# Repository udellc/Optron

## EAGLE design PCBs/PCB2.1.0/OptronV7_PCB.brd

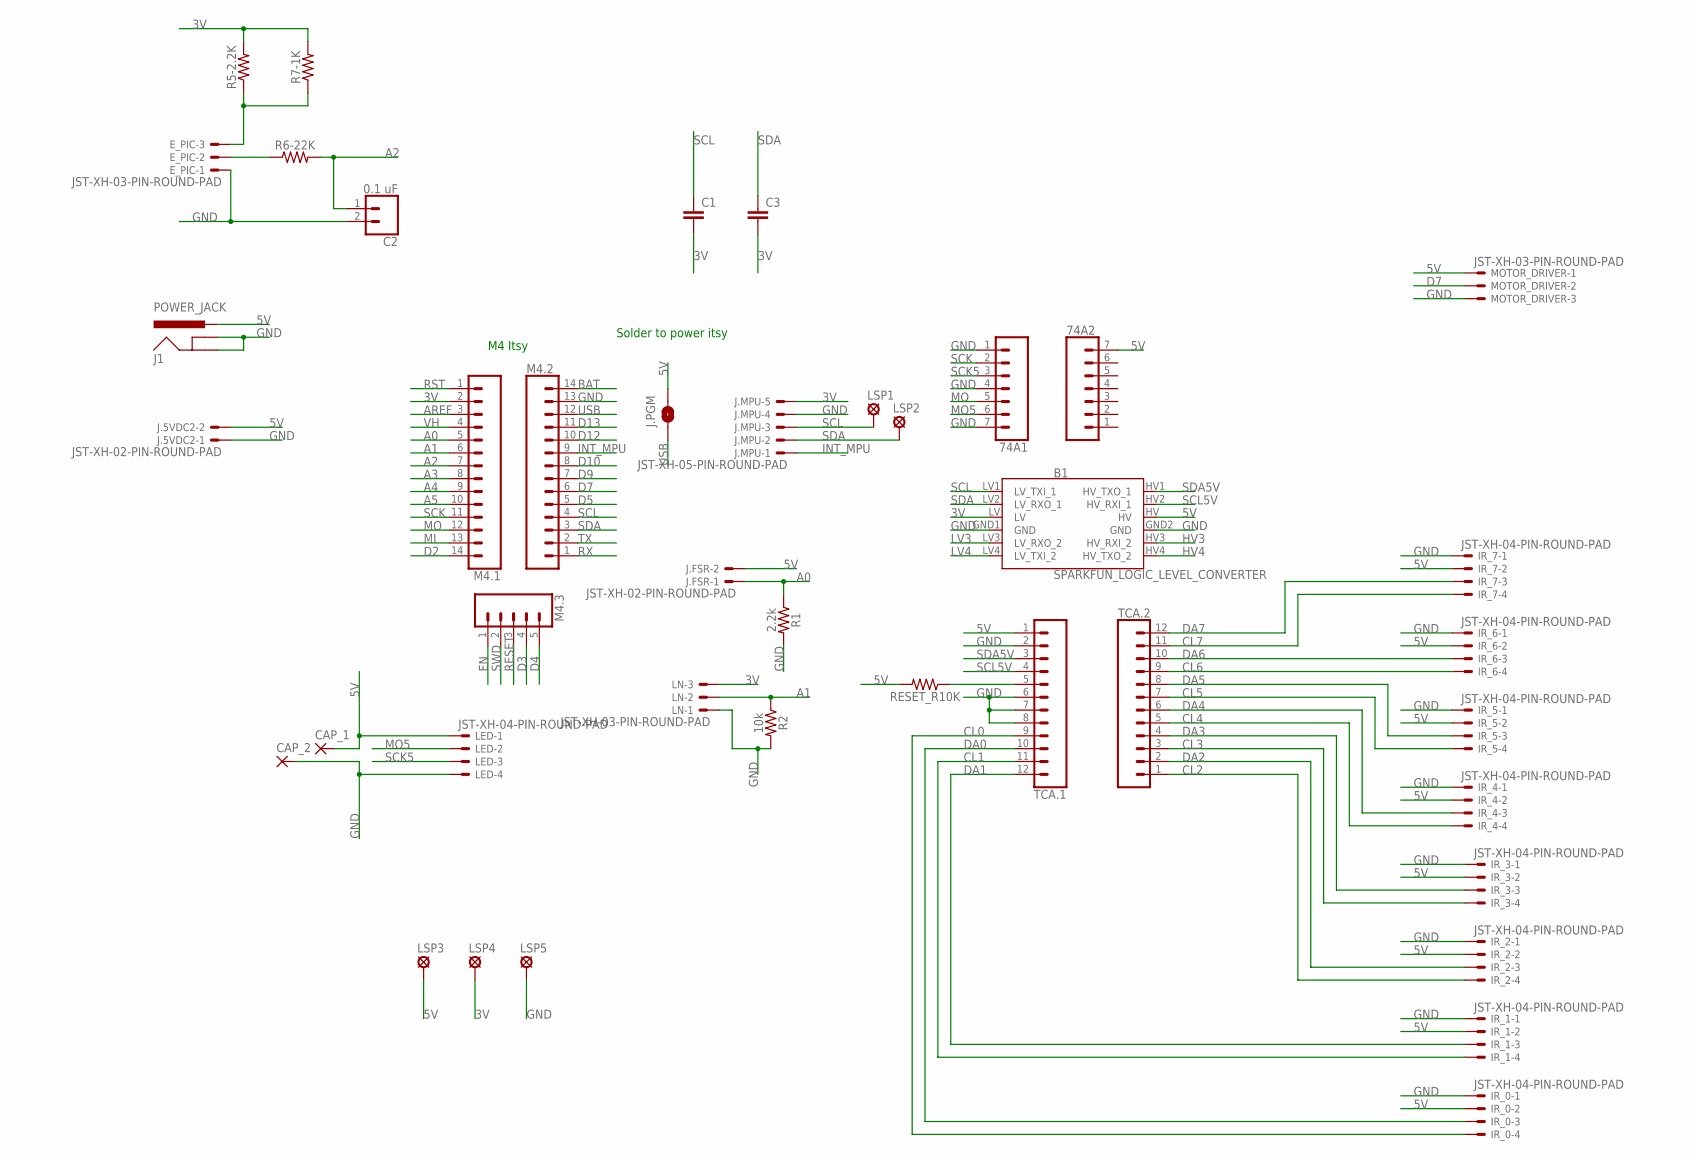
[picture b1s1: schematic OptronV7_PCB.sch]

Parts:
74A1, 74A2: CONN_07; 1X07
B1: SPARKFUN_LOGIC_LEVEL_CONVERTER
C1, C3: C5/2.5; C5B2.5
C2: 0.1 uF; 1X02
CAP_1, CAP_2: 1,6/0,8
E_PIC: JST-XH-03-PIN-ROUND-PAD; JST-XH-03-PACKAGE-ROUND-PAD
IR_0, IR_1, IR_2, IR_3, IR_4, IR_5, IR_6, IR_7: JST-XH-04-PIN-ROUND-PAD; JST-XH-04-PACKAGE-ROUND-PAD
J1: POWER_JACK; POWER_JACK_PTH
J.5VDC2, J.FSR: JST-XH-02-PIN-ROUND-PAD; JST-XH-02-PACKAGE-ROUND-PAD
J.MPU: JST-XH-05-PIN-ROUND-PAD; JST-XH-05-PACKAGE-ROUND-PAD
J.PGM: JUMPER-SMT_2_NO_NO-SILK; SMT-JUMPER_2_NO_NO-SILK
LED: JST-XH-04-PIN-ROUND-PAD; JST-XH-04-PACKAGE-ROUND-PAD
LN: JST-XH-03-PIN-ROUND-PAD; JST-XH-03-PACKAGE-ROUND-PAD
LSP1, LSP2, LSP3, LSP4, LSP5: MCS08
M4.1, M4.2: CONN_14; 1X14
M4.3: CONN_05; 1X05
MOTOR_DRIVER: JST-XH-03-PIN-ROUND-PAD; JST-XH-03-PACKAGE-ROUND-PAD
R1: 2.2k; AXIAL-0.3
R2: 10k; AXIAL-0.3
R5-2.2K, R6-22K, R7-1K: AXIAL-0.3
RESET_R10K: AXIAL-0.3
TCA.1, TCA.2: CONN_12; 1X12

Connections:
3V: B1.LV, C1.2, C3.2, J.MPU.5, LN.3, LSP4.MP, M4.1.2, R5-2.2K.P$2 (2), R7-1K.P$2 (2)
5V: 74A2.7, B1.HV, CAP_1.1, IR_0.2, IR_1.2, IR_2.2, IR_3.2, IR_4.2, IR_5.2, IR_6.2, IR_7.2, J1.PWR, J.5VDC2.2, J.FSR.2, J.PGM.2, LED.1, LSP3.MP, MOTOR_DRIVER.1, RESET_R10K.P$2 (2), TCA.1.1
A0: J.FSR.1, M4.1.5, R1.P$1 (1)
A1: LN.2, M4.1.6, R2.P$1 (1)
A2: C2.1, M4.1.7, R6-22K.P$2 (2)
A3: M4.1.8
A4: M4.1.9
A5: M4.1.10
AREF: M4.1.3
BAT: M4.2.14
CL0: IR_0.4, TCA.1.9
CL1: IR_1.4, TCA.1.11
CL2: IR_2.4, TCA.2.1
CL3: IR_3.4, TCA.2.3
CL4: IR_4.4, TCA.2.5
CL5: IR_5.4, TCA.2.7
CL6: IR_6.4, TCA.2.9
CL7: IR_7.4, TCA.2.11
D2: M4.1.14
D3: M4.3.4
D4: M4.3.5
D5: M4.2.5
D7: M4.2.6, MOTOR_DRIVER.2
D9: M4.2.7
D10: M4.2.8
D12: M4.2.10
D13: M4.2.11
DA0: IR_0.3, TCA.1.10
DA1: IR_1.3, TCA.1.12
DA2: IR_2.3, TCA.2.2
DA3: IR_3.3, TCA.2.4
DA4: IR_4.3, TCA.2.6
DA5: IR_5.3, TCA.2.8
DA6: IR_6.3, TCA.2.10
DA7: IR_7.3, TCA.2.12
EN: M4.3.1
GND: 74A1.1, 74A1.4, 74A1.7, B1.GND1 (GND), B1.GND2 (GND), C2.2, CAP_2.1, E_PIC.1, IR_0.1, IR_1.1, IR_2.1, IR_3.1, IR_4.1, IR_5.1, IR_6.1, IR_7.1, J1.GND, J1.GNDBREAK, J.5VDC2.1, J.MPU.4, LED.4, LN.1, LSP5.MP, M4.2.13, MOTOR_DRIVER.3, R1.P$2 (2), R2.P$2 (2), TCA.1.2, TCA.1.6, TCA.1.7, TCA.1.8
HV3: B1.HV3 (HV_RXI_2)
HV4: B1.HV4 (HV_TXO_2)
INT_MPU: J.MPU.1, M4.2.9
LV3: B1.LV3 (LV_RXO_2)
LV4: B1.LV4 (LV_TXI_2)
MI: M4.1.13
MO: 74A1.5, M4.1.12
MO5: 74A1.6, LED.2
unnamed: RESET_R10K.P$1 (1), TCA.1.5
unnamed: E_PIC.3, R5-2.2K.P$1 (1), R7-1K.P$1 (1)
unnamed: E_PIC.2, R6-22K.P$1 (1)
RESET: M4.3.3
RST: M4.1.1
RX: M4.2.1
SCK: 74A1.2, M4.1.11
SCK5: 74A1.3, LED.3
SCL: B1.LV1 (LV_TXI_1), C1.1, J.MPU.3, LSP1.MP, M4.2.4
SCL5V: B1.HV2 (HV_RXI_1), TCA.1.4
SDA: B1.LV2 (LV_RXO_1), C3.1, J.MPU.2, LSP2.MP, M4.2.3
SDA5V: B1.HV1 (HV_TXO_1), TCA.1.3
SWD: M4.3.2
TX: M4.2.2
USB: J.PGM.1, M4.2.12
VH: M4.1.4

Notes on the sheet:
M4 Itsy
Solder to power itsy

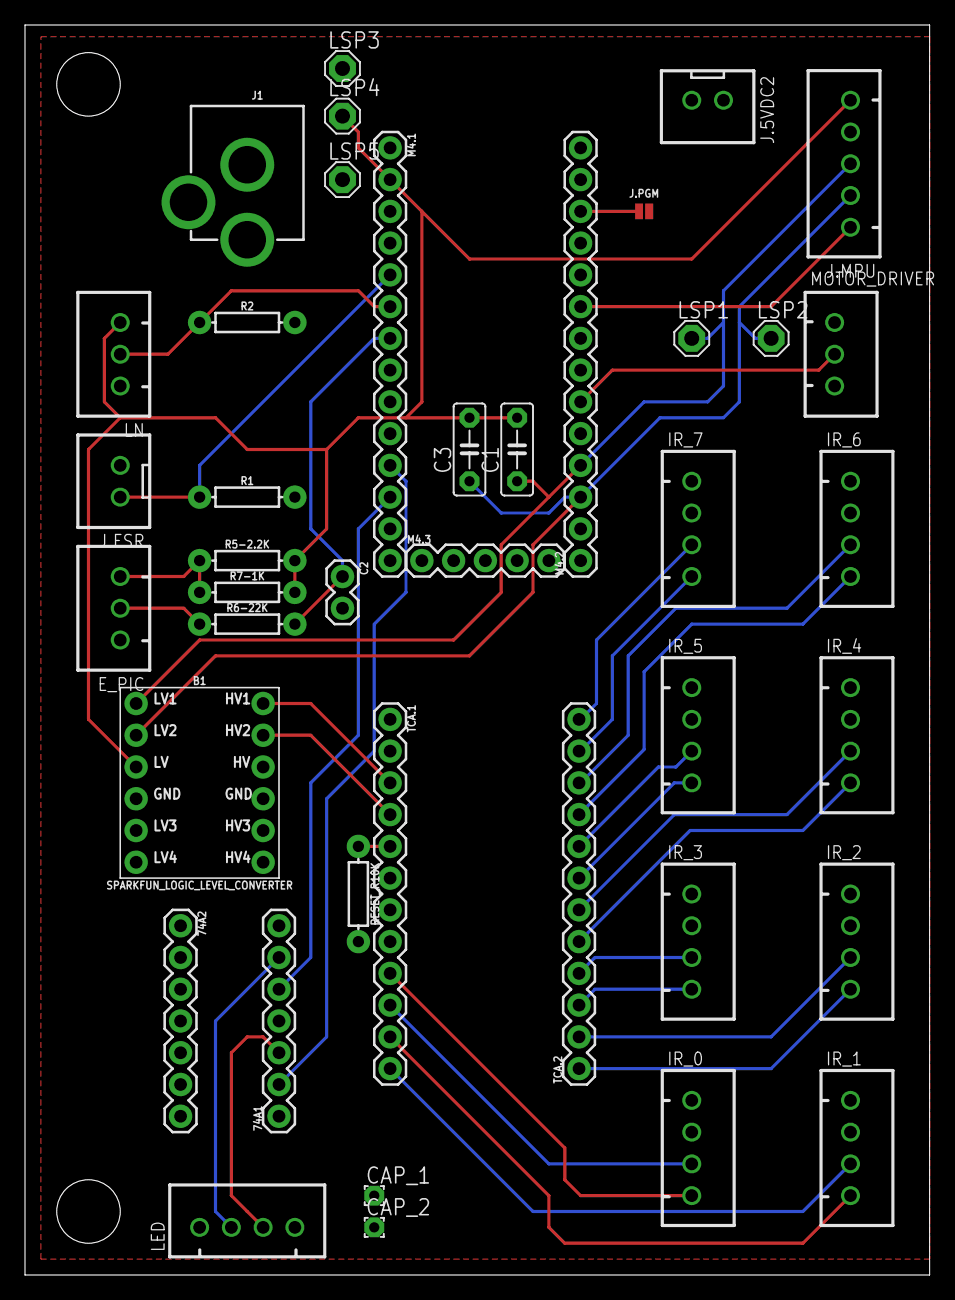
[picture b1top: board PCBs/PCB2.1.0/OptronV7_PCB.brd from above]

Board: 2 copper layers, 72.4 x 100.0 mm, 41 parts (0 on the bottom side), 36 nets.

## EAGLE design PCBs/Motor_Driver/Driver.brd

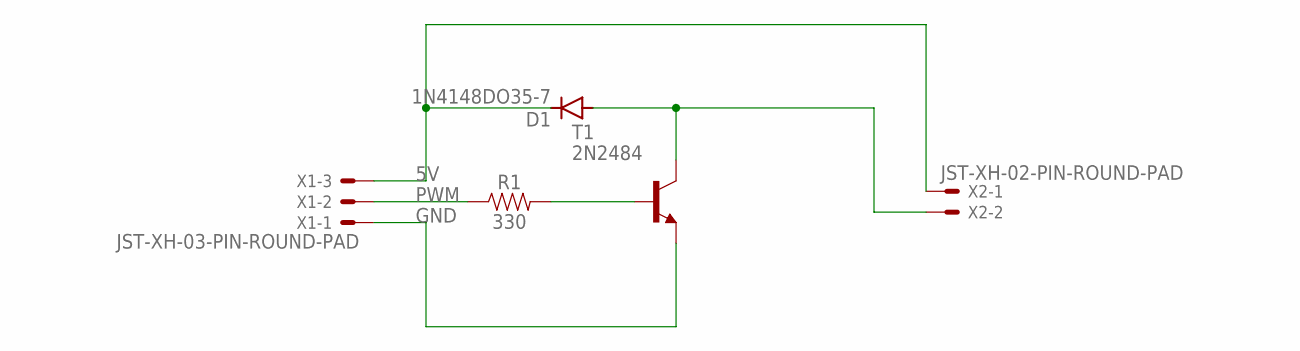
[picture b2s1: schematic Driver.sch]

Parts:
D1: 1N4148DO35-7; DO35-7
R1: 330; AXIAL-0.3
T1: 2N2484; TO18
X1: JST-XH-03-PIN-ROUND-PAD; JST-XH-03-PACKAGE-ROUND-PAD
X2: JST-XH-02-PIN-ROUND-PAD; JST-XH-02-PACKAGE-ROUND-PAD

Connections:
5V: D1.C, X1.3, X2.1
GND: T1.1 (E), X1.1
unnamed: R1.P$2 (2), T1.2 (B)
unnamed: D1.A, T1.3 (C), X2.2
PWM: R1.P$1 (1), X1.2

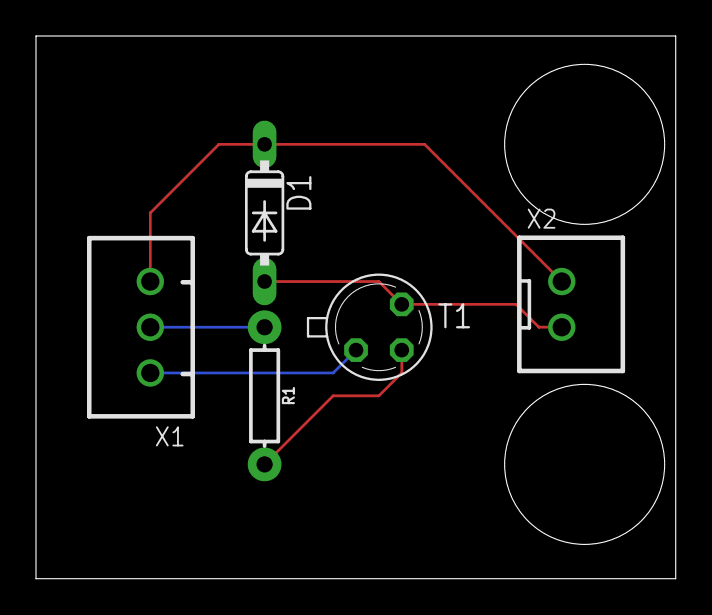
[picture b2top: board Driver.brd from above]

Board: 2 copper layers, 35.5 x 30.1 mm, 5 parts (0 on the bottom side), 5 nets.

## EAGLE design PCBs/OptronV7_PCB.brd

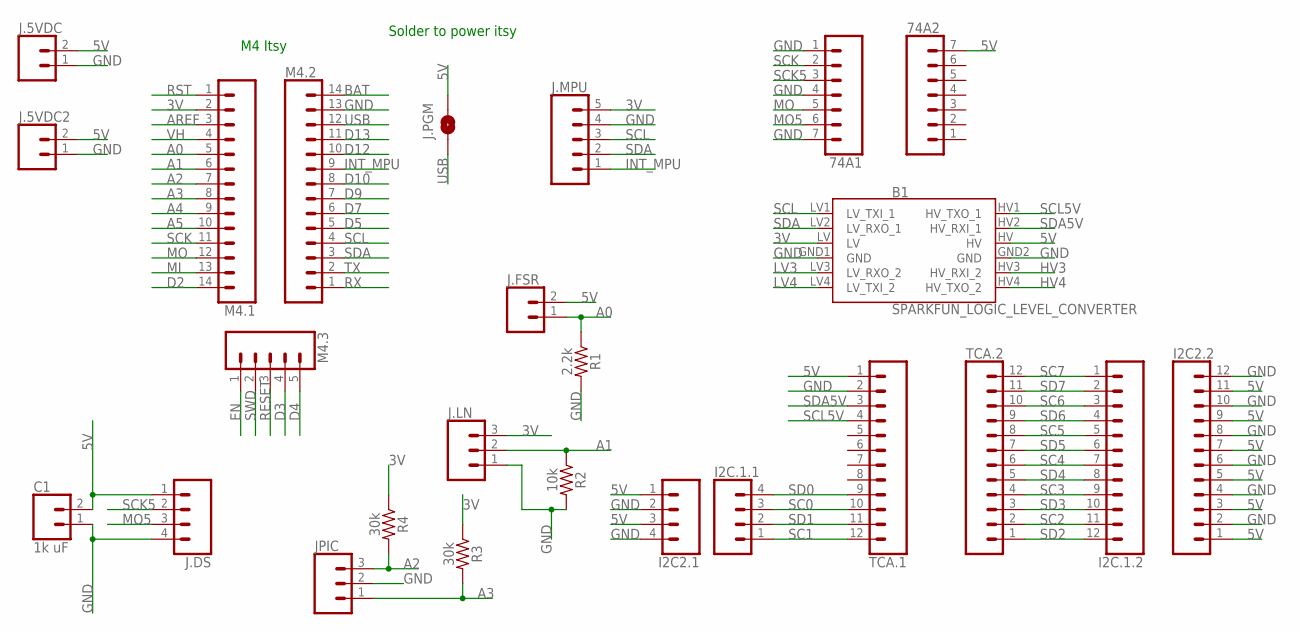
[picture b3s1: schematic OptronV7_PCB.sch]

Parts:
74A1, 74A2: CONN_07; 1X07
B1: SPARKFUN_LOGIC_LEVEL_CONVERTER
C1: 1k uF; 1X02
I2C2.1, I2C.1.1: CONN_04; 1X04
I2C2.2, I2C.1.2: CONN_12; 1X12
J.5VDC, J.5VDC2, J.FSR: CONN_02; 1X02
J.DS: CONN_04; 1X04
J.LN: CONN_03; 1X03
J.MPU: CONN_05; 1X05
J.PGM: JUMPER-SMT_2_NO_NO-SILK; SMT-JUMPER_2_NO_NO-SILK
JPIC: CONN_03; 1X03
M4.1, M4.2: CONN_14; 1X14
M4.3: CONN_05; 1X05
R1: 2.2k; AXIAL-0.3
R2: 10k; AXIAL-0.3
R3, R4: 30k; AXIAL-0.3
TCA.1, TCA.2: CONN_12; 1X12

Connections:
3V: B1.LV, J.LN.3, J.MPU.5, M4.1.2, R3.P$1 (1), R4.P$1 (1)
5V: 74A2.7, B1.HV, C1.2, I2C2.1.1, I2C2.1.3, I2C2.2.1, I2C2.2.3, I2C2.2.5, I2C2.2.7, I2C2.2.9, I2C2.2.11, J.5VDC.2, J.5VDC2.2, J.DS.1, J.FSR.2, J.PGM.2, TCA.1.1
A0: J.FSR.1, M4.1.5, R1.P$1 (1)
A1: J.LN.2, M4.1.6, R2.P$1 (1)
A2: JPIC.3, M4.1.7, R4.P$2 (2)
A3: JPIC.1, M4.1.8, R3.P$2 (2)
A4: M4.1.9
A5: M4.1.10
AREF: M4.1.3
BAT: M4.2.14
D2: M4.1.14
D3: M4.3.4
D4: M4.3.5
D5: M4.2.5
D7: M4.2.6
D9: M4.2.7
D10: M4.2.8
D12: M4.2.10
D13: M4.2.11
EN: M4.3.1
GND: 74A1.1, 74A1.4, 74A1.7, B1.GND1 (GND), B1.GND2 (GND), C1.1, I2C2.1.2, I2C2.1.4, I2C2.2.2, I2C2.2.4, I2C2.2.6, I2C2.2.8, I2C2.2.10, I2C2.2.12, J.5VDC.1, J.5VDC2.1, J.DS.4, J.LN.1, J.MPU.4, JPIC.2, M4.2.13, R1.P$2 (2), R2.P$2 (2), TCA.1.2
HV3: B1.HV3 (HV_RXI_2)
HV4: B1.HV4 (HV_TXO_2)
INT_MPU: J.MPU.1, M4.2.9
LV3: B1.LV3 (LV_RXO_2)
LV4: B1.LV4 (LV_TXI_2)
MI: M4.1.13
MO: 74A1.5, M4.1.12
MO5: 74A1.6, J.DS.3
RESET: M4.3.3
RST: M4.1.1
RX: M4.2.1
SC0: I2C.1.1.3, TCA.1.10
SC1: I2C.1.1.1, TCA.1.12
SC2: I2C.1.2.11, TCA.2.2
SC3: I2C.1.2.9, TCA.2.4
SC4: I2C.1.2.7, TCA.2.6
SC5: I2C.1.2.5, TCA.2.8
SC6: I2C.1.2.3, TCA.2.10
SC7: I2C.1.2.1, TCA.2.12
SCK: 74A1.2, M4.1.11
SCK5: 74A1.3, J.DS.2
SCL: B1.LV1 (LV_TXI_1), J.MPU.3, M4.2.4
SCL5V: B1.HV1 (HV_TXO_1), TCA.1.4
SD0: I2C.1.1.4, TCA.1.9
SD1: I2C.1.1.2, TCA.1.11
SD2: I2C.1.2.12, TCA.2.1
SD3: I2C.1.2.10, TCA.2.3
SD4: I2C.1.2.8, TCA.2.5
SD5: I2C.1.2.6, TCA.2.7
SD6: I2C.1.2.4, TCA.2.9
SD7: I2C.1.2.2, TCA.2.11
SDA: B1.LV2 (LV_RXO_1), J.MPU.2, M4.2.3
SDA5V: B1.HV2 (HV_RXI_1), TCA.1.3
SWD: M4.3.2
TX: M4.2.2
USB: J.PGM.1, M4.2.12
VH: M4.1.4

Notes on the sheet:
M4 Itsy
Solder to power itsy

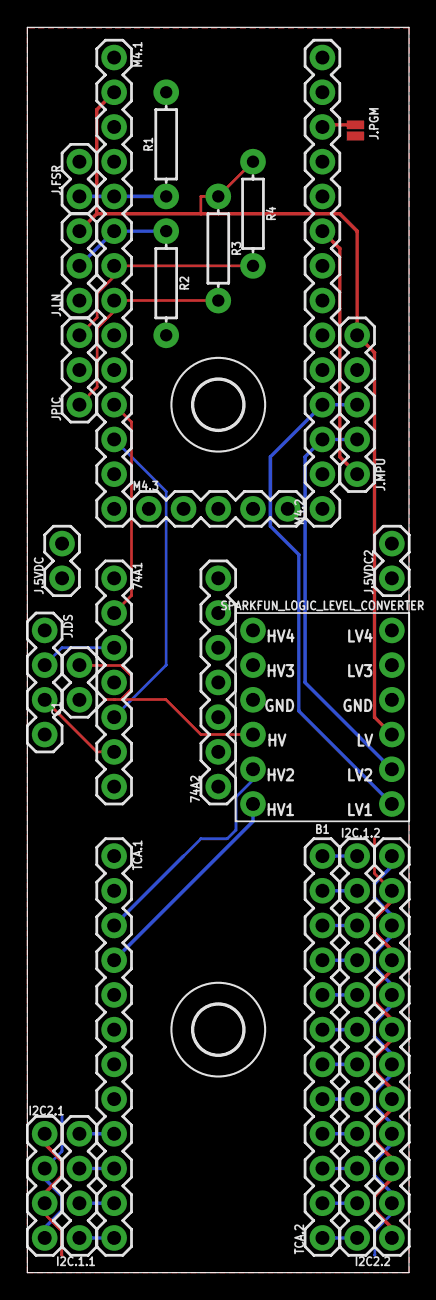
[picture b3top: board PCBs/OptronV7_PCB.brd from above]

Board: 2 copper layers, 27.9 x 91.1 mm, 27 parts (0 on the bottom side), 33 nets.

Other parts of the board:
U$1, U$2: 3,6

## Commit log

2019-10-12 Optron V7 Main Adapter Board
2019-10-22 Extrusion file from Misumi added
2019-11-11 necessary_libraries_SEE_README
2019-11-21 Added ZX Gesture Sensor Mount 2.1
2019-11-22 Fixed MPU6050 Library and function declarations
2019-11-22 Added ZX Gesture Sensor Long Mount Clip STL
2019-11-25 Added 11_24 RGBdemo
2019-11-25 Refactored rgb demo to new location and name
2020-01-07 Added fret board stl's, wire manager stl's, and gesture sensor mount
2020-01-07 Separated 2.0 and 2.1 STLs
2020-01-07 Added pcb mount
2020-01-07 Updated and added STL files
2020-01-12 Added some images
2020-01-15 Updated STLs
2020-01-17 Added gcode of parts.
2020-01-21 Added an Optron2.1 build guide rough draft
2020-01-21 Added some cool images
2020-01-22 Animation_Pattern
2020-01-22 Added MPU6050 class. It is a frame right now that needs to be filled in.
2020-01-31 Object-Oriented Code with multi-pattern
2020-01-31 Added firmware functions for MPU6050.
2020-02-07 Added a bunch of assembly images
2020-02-07 Added some images and edited others
2020-02-08 Adding New PCB
2020-02-09 Added a demo for branch. Works on teensy2.0.
2020-02-09 Added accel demo, and removed mympu class from main code
2020-02-12 Updated Build Guide.
2020-02-12 Added a bunch of images from the cad model.
2020-02-12 serialinput not looping
2020-02-17 Added PCBs and Schematics
2020-02-18 Added sliding wire manager strap mount with mpu mount.
2020-02-20 Added teflon dxf
2020-02-28 added json file, constructors testing
2020-03-02 Added a demo for both IR and MPU at the same time
2020-03-04 Updated IR/ACCEL demo
2020-03-10 Reorganized debug statements, and activated all peripherals.
2020-03-10 Added new PCB mount cad file
2020-03-10 Added EPick wire manager and Fretboard wire manager CAD files
2020-03-10 Added BOM for Optron2.1
2020-03-12 Created a demo program for the Optron2.1
2020-04-08 Finished with on/off pattern by command
2020-04-10 Added newest version of the PCB for review and requests for more additions.
2020-04-17 Add files via upload
    E-Pick code 1.1
2020-04-17 PCB 2.1.0 added
2020-04-20 Added and moved a bunch of images.
2020-04-20 Updated BOM
2020-04-20 Updated build guide
2020-04-28 Updated Build Guide and added some photos
2020-04-30 updated Optron
2020-05-01 PCB review updates
2020-05-02 Added brightness change-fretboard pressure
2020-05-03 Deleted previous main code in folder 'Optron2_1' and put current working code into folder titled 'Optron2.2'
2020-05-03 Made code more organized, and added toggle defines for sensing MPU and ZX sensors.
2020-05-03 Added masking of LEDs based on position sensor.
2020-05-04 Added non-destructive masking ability.
2020-05-04 Added some small bug fixes to masking.
2020-05-05 Added lighting control via IR sensors. Also added another sensor control panel for LEDs, and fixed up som ee-pick code.
2020-05-20 added doxygen html file
2020-05-27 added program flow diagram
2020-08-27 large update
2020-12-01 ICST
2020-12-01 crystal
2021-01-15 M4Animation

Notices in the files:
parts and their libraries:
SparkFun-Resistors: Licensing: Creative Commons ShareAlike 4.0 International - https://creativecommons.org/licenses/by-sa/4.0
